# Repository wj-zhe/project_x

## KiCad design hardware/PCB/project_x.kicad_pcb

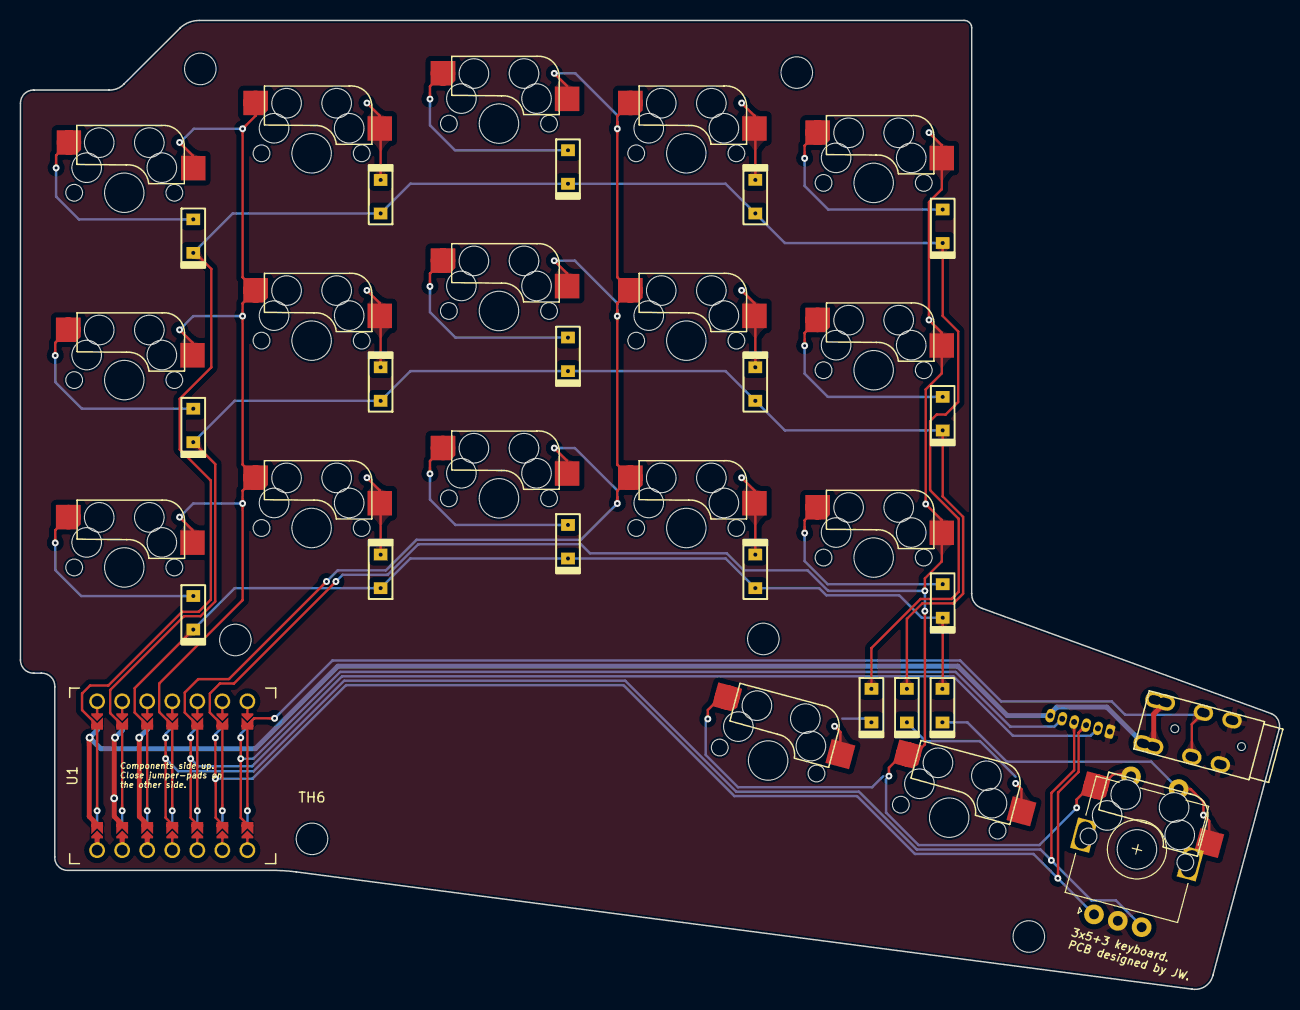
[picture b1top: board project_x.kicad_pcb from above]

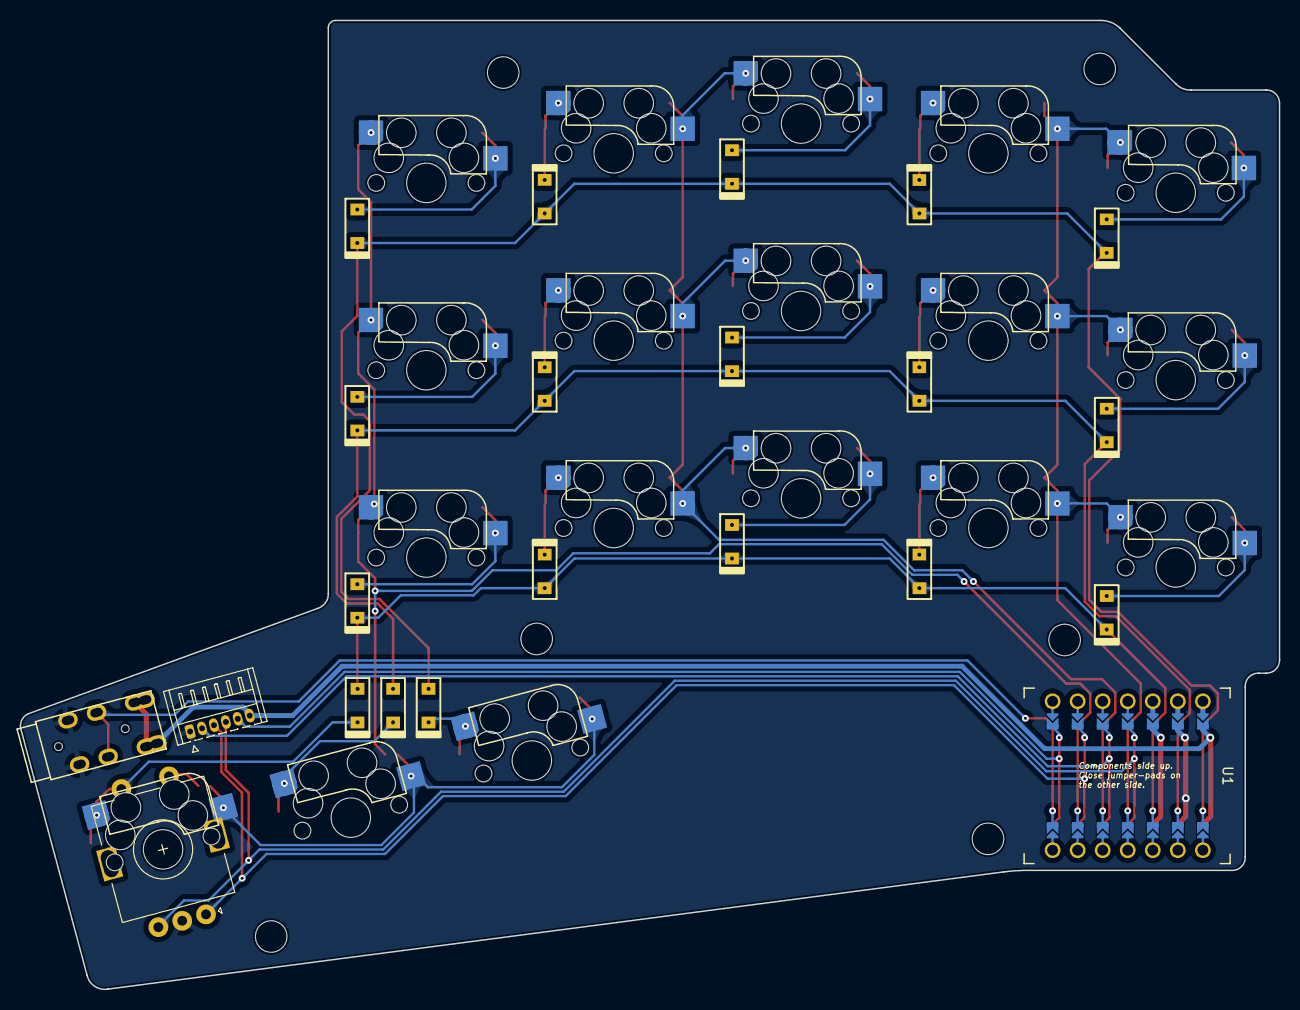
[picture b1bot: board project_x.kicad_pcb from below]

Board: 2 copper layers, 127.7 x 98.3 mm, 46 parts (3 on the bottom side), 31 nets.

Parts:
D1, D2, D3, D4, D5, D6, D7, D8, D9, D10, D11, D12, D13, D14, D15, D16, D17, D18: Diode; Diode_SOD123_THT_2
EC1: Rotary_Encoder_Switch; RotaryEncoder_Alps_EC11E-Switch_Vertical_H20mm
J1: 4PIN; TRRS-PJ-DPB2_mod
J2: Conn_01x06_Female; Hirose_DF13-06P-1.25DS_1x06_P1.25mm_Horizontal
SW1: SW1; CherryMX_Hotswap
SW2: SW2; CherryMX_Hotswap
SW3: SW3; CherryMX_Hotswap
SW4: SW4; CherryMX_Hotswap
SW5: SW5; CherryMX_Hotswap
SW6: SW6; CherryMX_Hotswap
SW7: SW7; CherryMX_Hotswap
SW8: SW8; CherryMX_Hotswap
SW9: SW9; CherryMX_Hotswap
SW10: SW10; CherryMX_Hotswap
SW11: SW11; CherryMX_Hotswap
SW12: SW12; CherryMX_Hotswap
SW13: SW13; CherryMX_Hotswap
SW14: SW14; CherryMX_Hotswap
SW15: SW15; CherryMX_Hotswap
SW16: SW16; CherryMX_Hotswap
SW17: SW17; CherryMX_Hotswap
SW18: SW18; CherryMX_Hotswap
TH1, TH2, TH3, TH4, TH5, TH6: HOLE; MountingHole_3.2mm_M3
U1: SeeeduinoXIAO; Xiao THT jumper pad_flipped

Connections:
DATA: J1.2, U1.7 (PB08_A6_D6_TX)
GND: EC1.C, J1.3, J2.1, U1.13 (GND)
MISO: J2.2, U1.10 (PA5_A9_D9_MISO)
MOSI_ENCB: EC1.B, J2.4, U1.11 (PA6_A10_D10_MOSI)
NCS: J2.5, U1.8 (PB09_A7_D7_RX)
unnamed: D1.2 (A), SW1.2
unnamed: D2.1 (K), SW2.2
unnamed: D3.2 (A), SW3.1
unnamed: D4.1 (K), SW4.2
unnamed: D5.2 (A), SW5.1
unnamed: D6.2 (A), SW6.1
unnamed: D7.1 (K), SW7.2
unnamed: D8.2 (A), SW8.1
unnamed: D9.1 (K), SW9.2
unnamed: D10.2 (A), SW10.1
unnamed: D11.2 (A), SW11.1
unnamed: D12.1 (K), SW12.2
unnamed: D13.2 (A), SW13.1
unnamed: D14.1 (K), SW14.2
unnamed: D15.2 (A), SW15.1
unnamed: D16.1 (K), SW16.2
unnamed: D17.1 (K), SW17.2
SCLK_ENCA: EC1.A, J2.3, U1.9 (PA7_A8_D8_SCK)
VDD_5V: J1.1, J1.4, J2.6, U1.14 (5V)
col0: SW1.1, SW2.1, SW6.2, SW7.1, SW11.2, SW12.1, U1.4 (PA11_A3_D3)
col1: SW3.2, SW4.1, SW8.2, SW9.1, SW13.2, SW14.1, U1.5 (PA8_A4_D4_SDA)
col2: EC1.S2, SW5.2, SW10.2, SW15.2, SW16.1, SW17.1, SW18.1, U1.6 (PA9_A5_D5_SCL)
row0: D1.1 (K), D2.2 (A), D3.1 (K), D4.2 (A), D5.1 (K), D16.2 (A), U1.1 (PA02_A0_D0)
row1: D6.1 (K), D7.2 (A), D8.1 (K), D9.2 (A), D10.1 (K), D17.2 (A), U1.2 (PA4_A1_D1)
row2: D11.1 (K), D12.2 (A), D13.1 (K), D14.2 (A), D15.1 (K), D18.2 (A), U1.3 (PA10_A2_D2)
sw_row: D18.1 (K), EC1.S1, SW18.2

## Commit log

2023-09-10 Trying duplex matrix
2023-11-20 Updated firmware.
2024-02-12 1. added hardware files; 2. updated fireware codes.
